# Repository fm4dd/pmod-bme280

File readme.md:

## BME280 PMOD

### Description

This PMOD connects the Bosch BME280 humidity, pressure and temperature sensor over I2C, using Digilent's PMOD interface type 6A per PMOD specification v1.3.1. The PMOD module can be chained to add additional I2C devices to the bus. The I2C pull-up resistors can be enabled/disabled using DIP switches, and switch 2 toggles the sensors I2C address between 0x76 and 0x77.

http://fpga.fm4dd.com/

This design is registered under the OSHWA Open Source Hardware Self-Certification:

### Schematic

### PCB Gerber
[BME280 PMOD Gerber V1.0](20220624-bme280-gerber-v10.zip)

### PMOD Interface Pin Assignments

Pin  |	Label |	Description   | Pin  |	Label |	Description
-----|--------|---------------|------|--------|---------------
1    |	-     |	Not connected |7     | -      | Not connected
2    |	-     |	Not connected |8     | -      | Not connected
3    |	SCL   |	I2C clock     |9     | -      | Not connected
4    |  SDA   | I2C data      |10    | -      | Not connected
5    |  GND   | ground        |11    | GND    | ground
6    |  3V3   | 3.3V          |12    | 3V3    | 3.3V

All pins are passed through from connector J1 to J2, allowing to chain multiple type 6/6A PMODs.

### Example Code

#### Linux

Above shows the BME280 PMOD, connected to a [PMOD2RPI](https://github.com/fm4dd/pmod2rpi) interface board. When connected through the PMOD4 connector, the module can be controlled from the Raspberry Pi 4 Linux, running the [pi-bme280](https://github.com/fm4dd/pi-bme280) control program.

#### Arduino

Without any changes, we can run BME280 sample code such as the [BMx280_I2C](https://bitbucket.org/christandlg/bmx280mi/src/master/examples/BMx280_I2C/BMx280_I2C.ino) example program from the BMx280MI library provided by Gregor Christandl. The BME280 PMOD module is connected to the [PMOD2RPI](https://github.com/fm4dd/pmod2rpi) interface board. On port PMOD1, the module communicates over I2C with the onboard Seeedstudio XIAO Cortex-M0 MCU.

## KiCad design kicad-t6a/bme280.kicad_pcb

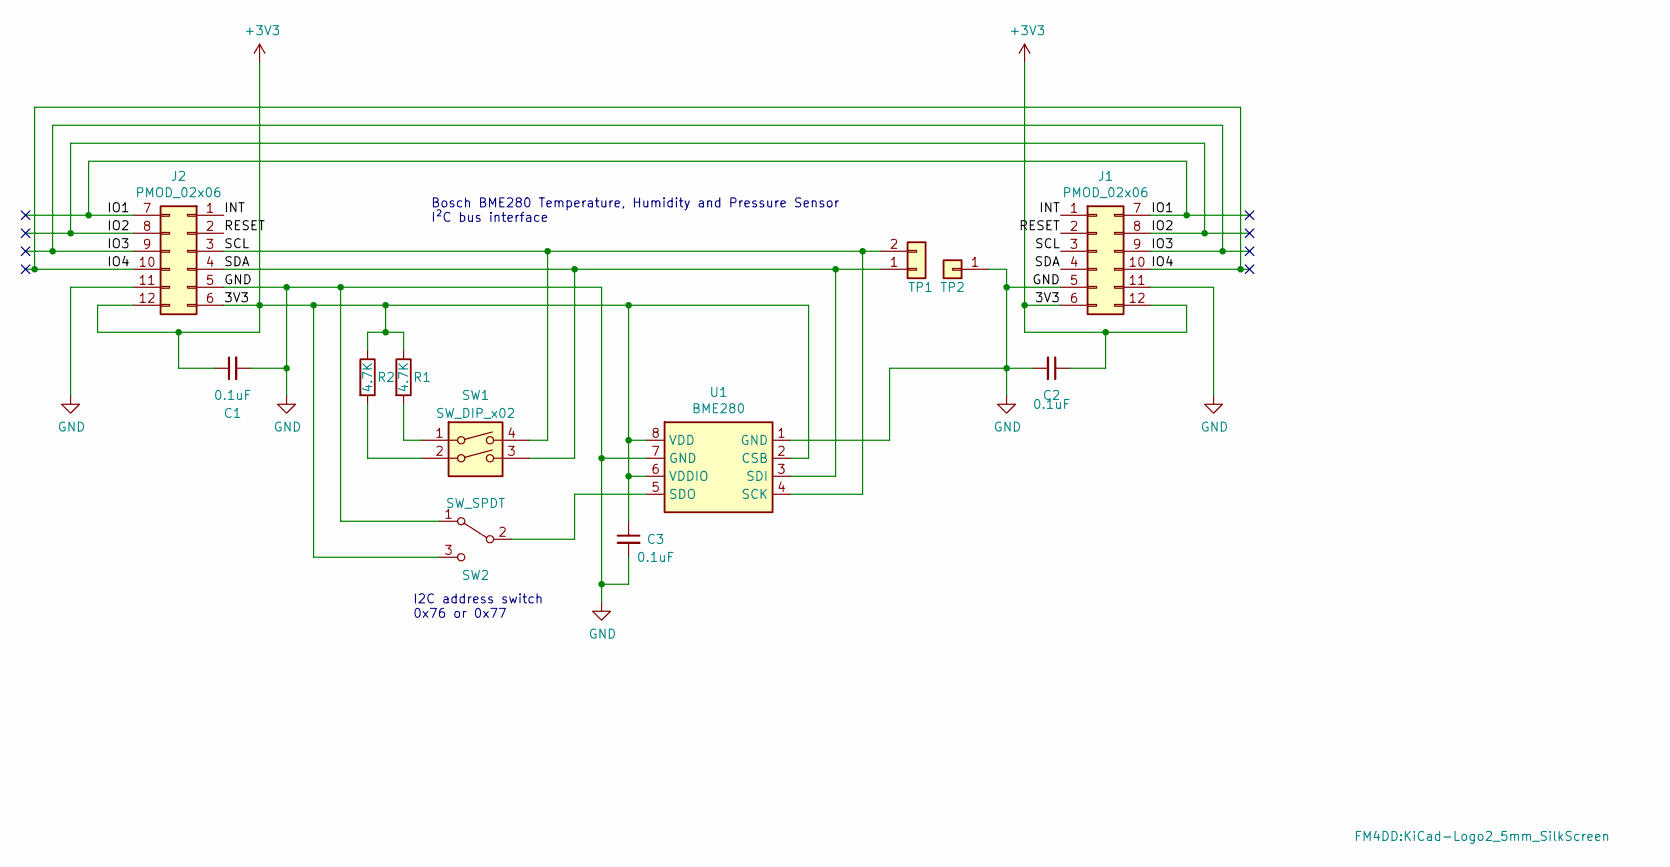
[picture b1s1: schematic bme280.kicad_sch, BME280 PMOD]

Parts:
C1, C2, C3: 0.1uF; C_0402_1005Metric
J1: PMOD_02x06; PMODPinSocket_2x06_P2.54mm_Horizontal
J2: PMOD_02x06; PMODHeader_2x06_P2.54mm_Horizontal
L1: Logo_KiCad_5mm; KiCad-Logo2_5mm_SilkScreen
R1, R2: 4.7K; R_0603_1608Metric
SW1: SW_DIP_x02; SW_DIP_SPSTx02_Slide_6.7x6.64mm_W7.62mm_P2.54mm_LowProfile
SW2: SW_SPDT; SW_SPDT_XKB-SS-3292S
TP1: Conn_01x02; Testpoint_PinHeader_1x02_P2.54mm_Vertical
TP2: TestPoint_Conn_01x01; TestPoint_PinHeader_1x01_P2.54mm_Vertical
U1: BME280; Bosch_LGA-8_2.5x2.5mm_P0.65mm_ClockwisePinNumbering

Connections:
+3V3: C1.1, C2.1, C3.1, J1.6, J1.12, J2.6, J2.12, R1.1, R2.1, SW2.3 (C), U1.2 (CSB), U1.6 (VDDIO), U1.8 (VDD)
/INT: J1.1, J2.1
/IO1: J1.7, J2.7
/IO2: J1.8, J2.8
/IO3: J1.9, J2.9
/IO4: J1.10, J2.10
/RESET: J1.2, J2.2
/SCL: J1.3, J2.3, SW1.4, TP1.2, U1.4 (SCK)
/SDA: J1.4, J2.4, SW1.3, TP1.1, U1.3 (SDI)
GND: C1.2, C2.2, C3.2, J1.5, J1.11, J2.5, J2.11, SW2.1 (A), TP2.1, U1.1 (GND), U1.7 (GND)
unnamed: R1.2, SW1.1
unnamed: R2.2, SW1.2
unnamed: SW2.2 (B), U1.5 (SDO)

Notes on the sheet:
I2C address switch 0x76 or 0x77
Bosch BME280 Temperature, Humidity and Pressure Sensor I²C bus interface

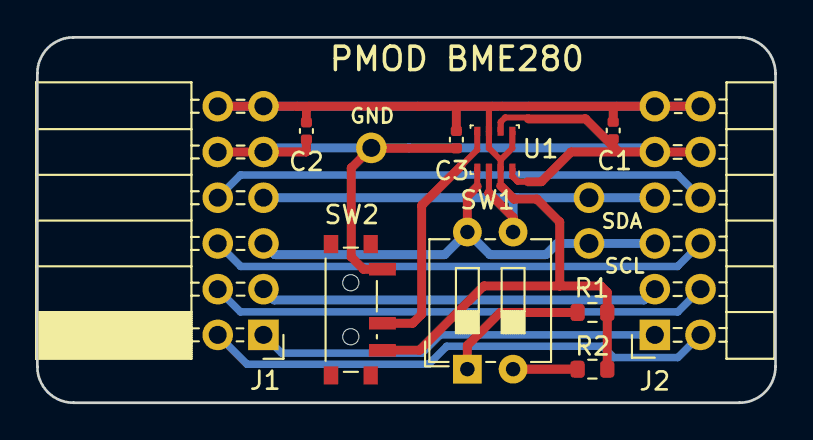
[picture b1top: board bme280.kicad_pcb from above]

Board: 2 copper layers, 41.0 x 20.3 mm, 14 parts (1 on the bottom side), 13 nets.

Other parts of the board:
Ref**: JLCPCB_Order_Number_Placeholder

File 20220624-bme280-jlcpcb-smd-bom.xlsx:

Comment | Designator | Footprint | LCSC Part #（optional）
BME280 | U1 | LGA-8_2.5x2.5x0.65P | C92489
SPDT | SW2 | Switch_SMD:SW_12mm | C397350
4.7K | R2,R1 | Resistor_SMD:R_0603_1608Metric
100nF | C3,C2,C1 | Capacitor_SMD:C_0402Metric

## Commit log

2022-07-04 repo init
2022-07-18 add OSHW cert

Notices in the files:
kicad-t6a/bme280.kicad_pcb:
License: CC-BY-SA 4.0
